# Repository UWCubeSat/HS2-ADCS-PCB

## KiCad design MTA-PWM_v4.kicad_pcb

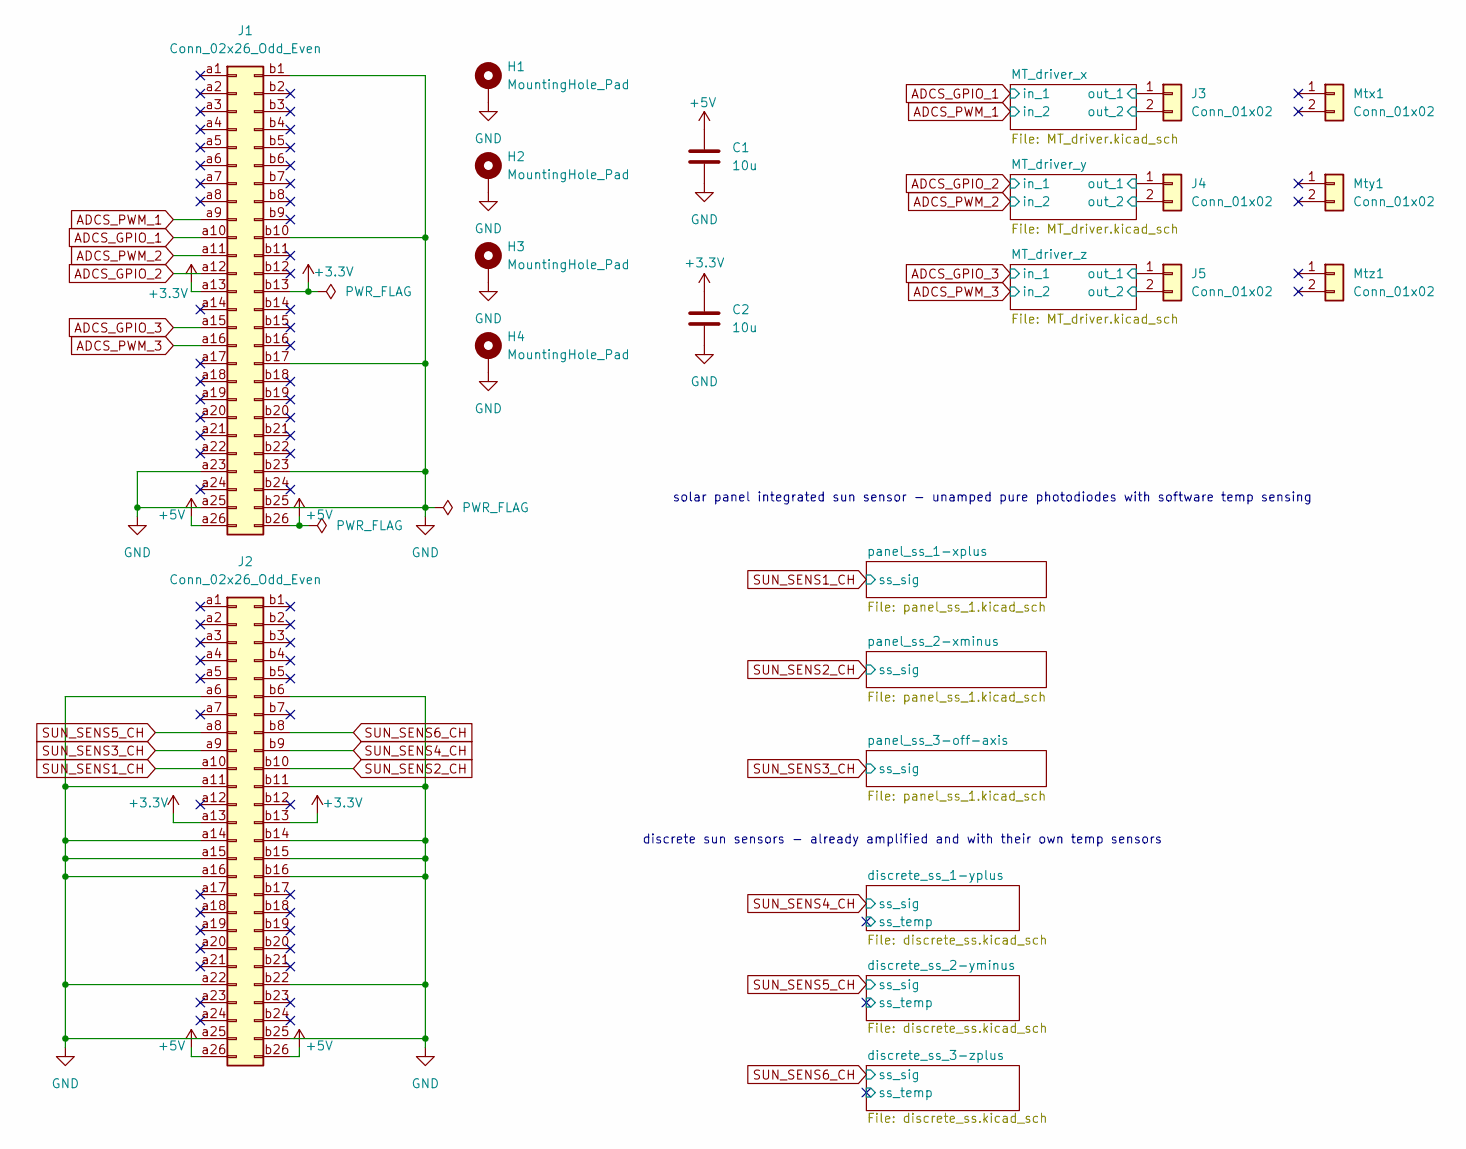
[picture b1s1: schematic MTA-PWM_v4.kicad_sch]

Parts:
C1, C2: 10u; C_Radial_D6.3mm_H11.0mm_P2.50mm
H1, H2, H3, H4: MountingHole_Pad; MountingHole_3.2mm_M3_Pad_TopBottom
J1, J2: Conn_02x26_Odd_Even; PC140Header_2x26_P2.54mm_Vertical
J3, J4: Conn_01x02; Molex_Pico-Lock_205338-0002_1x02-1MP_P2.00mm_Horizontal
J5: Conn_01x02; Molex_PicoBlade_53261-0271_1x02-1MP_P1.25mm_Horizontal
Mtx1: Conn_01x02; MT_CS0002-G2
Mty1: Conn_01x02; MT_CS0002-G2R
Mtz1: Conn_01x02; MTR_EXA

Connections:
+3.3V: C2.1, J1.a13, J1.b13, J2.a13, J2.b13; also elsewhere on the board
+5V: C1.1, J1.a26, J1.b26, J2.a26, J2.b26; also elsewhere on the board
/MT_driver_x/out_1: J3.1; also elsewhere on the board
/MT_driver_x/out_2: J3.2; also elsewhere on the board
/MT_driver_y/out_1: J4.1; also elsewhere on the board
/MT_driver_y/out_2: J4.2; also elsewhere on the board
/MT_driver_z/out_1: J5.1; also elsewhere on the board
/MT_driver_z/out_2: J5.2; also elsewhere on the board
ADCS_GPIO_1: J1.a10; also elsewhere on the board
ADCS_GPIO_2: J1.a12; also elsewhere on the board
ADCS_GPIO_3: J1.a15; also elsewhere on the board
ADCS_PWM_1: J1.a9; also elsewhere on the board
ADCS_PWM_2: J1.a11; also elsewhere on the board
ADCS_PWM_3: J1.a16; also elsewhere on the board
GND: C1.2, C2.2, H1.1 (1_1), H2.1 (1_1), H3.1 (1_1), H4.1 (1_1), J1.a23, J1.a25, J1.b1, J1.b10, J1.b17, J1.b23, J1.b25, J2.a6, J2.a11, J2.a14, J2.a15, J2.a16, J2.a22, J2.a25, J2.b6, J2.b11, J2.b14, J2.b15, J2.b16, J2.b22, J2.b25; also elsewhere on the board
SUN_SENS1_CH: J2.a10; also elsewhere on the board
SUN_SENS2_CH: J2.b10; also elsewhere on the board
SUN_SENS3_CH: J2.a9; also elsewhere on the board
SUN_SENS4_CH: J2.b9; also elsewhere on the board
SUN_SENS5_CH: J2.a8; also elsewhere on the board
SUN_SENS6_CH: J2.b8; also elsewhere on the board

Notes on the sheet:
solar panel integrated sun sensor - unamped pure photodiodes with software temp sensing
discrete sun sensors - already amplified and with their own temp sensors

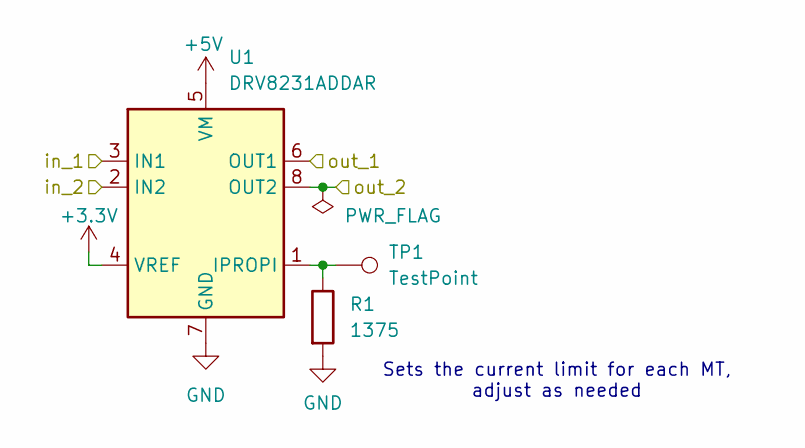
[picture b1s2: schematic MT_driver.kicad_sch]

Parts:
R1: 1375; R_Axial_DIN0207_L6.3mm_D2.5mm_P10.16mm_Horizontal
TP1: TestPoint; TestPoint_THTPad_1.5x1.5mm_Drill0.7mm
U1: DRV8231ADDAR; Texas_DSG0008A_WSON-8-1EP_2x2mm_P0.5mm_EP0.9x1.6mm

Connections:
+3.3V: U1.4 (VREF); also elsewhere on the board
+5V: U1.5 (VM); also elsewhere on the board
/MT_driver_x/out_1: U1.6 (OUT1); also elsewhere on the board
/MT_driver_x/out_2: U1.8 (OUT2); also elsewhere on the board
ADCS_GPIO_1: U1.3 (IN1); also elsewhere on the board
ADCS_PWM_1: U1.2 (IN2); also elsewhere on the board
GND: R1.2, U1.7 (GND), U1.9 (GND); also elsewhere on the board
unnamed: R1.1, TP1.1 (1_1), U1.1 (IPROPI)

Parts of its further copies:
R2, R3: 1375; R_Axial_DIN0207_L6.3mm_D2.5mm_P10.16mm_Horizontal
TP2, TP3: TestPoint; TestPoint_THTPad_1.5x1.5mm_Drill0.7mm
U2, U3: DRV8231ADDAR; Texas_DSG0008A_WSON-8-1EP_2x2mm_P0.5mm_EP0.9x1.6mm

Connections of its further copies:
+3.3V: U2.4 (VREF), U3.4 (VREF); also elsewhere on the board
+5V: U2.5 (VM), U3.5 (VM); also elsewhere on the board
/MT_driver_y/out_1: U2.6 (OUT1); also elsewhere on the board
/MT_driver_y/out_2: U2.8 (OUT2); also elsewhere on the board
/MT_driver_z/out_1: U3.6 (OUT1); also elsewhere on the board
/MT_driver_z/out_2: U3.8 (OUT2); also elsewhere on the board
ADCS_GPIO_2: U2.3 (IN1); also elsewhere on the board
ADCS_GPIO_3: U3.3 (IN1); also elsewhere on the board
ADCS_PWM_2: U2.2 (IN2); also elsewhere on the board
ADCS_PWM_3: U3.2 (IN2); also elsewhere on the board
GND: R2.2, R3.2, U2.7 (GND), U2.9 (GND), U3.7 (GND), U3.9 (GND); also elsewhere on the board
unnamed: R2.1, TP2.1 (1_1), U2.1 (IPROPI)
unnamed: R3.1, TP3.1 (1_1), U3.1 (IPROPI)

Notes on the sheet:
Sets the current limit for each MT, adjust as needed

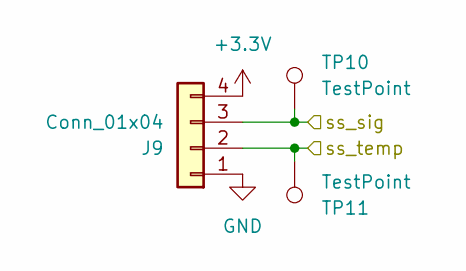
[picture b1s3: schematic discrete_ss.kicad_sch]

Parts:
J9: Conn_01x04; Molex_Pico-Lock_205338-0004_1x04-1MP_P2.00mm_Horizontal
TP10, TP11: TestPoint; TestPoint_THTPad_1.5x1.5mm_Drill0.7mm

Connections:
+3.3V: J9.4; also elsewhere on the board
/discrete_ss_1-yplus/ss_temp: J9.2, TP11.1 (1_1)
GND: J9.1; also elsewhere on the board
SUN_SENS4_CH: J9.3, TP10.1 (1_1); also elsewhere on the board

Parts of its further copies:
J10, J11: Conn_01x04; Molex_Pico-Lock_205338-0004_1x04-1MP_P2.00mm_Horizontal
TP12, TP13, TP14, TP15: TestPoint; TestPoint_THTPad_1.5x1.5mm_Drill0.7mm

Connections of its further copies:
+3.3V: J10.4, J11.4; also elsewhere on the board
/discrete_ss_2-yminus/ss_temp: J10.2, TP13.1 (1_1)
/discrete_ss_3-zplus/ss_temp: J11.2, TP15.1 (1_1)
GND: J10.1, J11.1; also elsewhere on the board
SUN_SENS5_CH: J10.3, TP12.1 (1_1); also elsewhere on the board
SUN_SENS6_CH: J11.3, TP14.1 (1_1); also elsewhere on the board

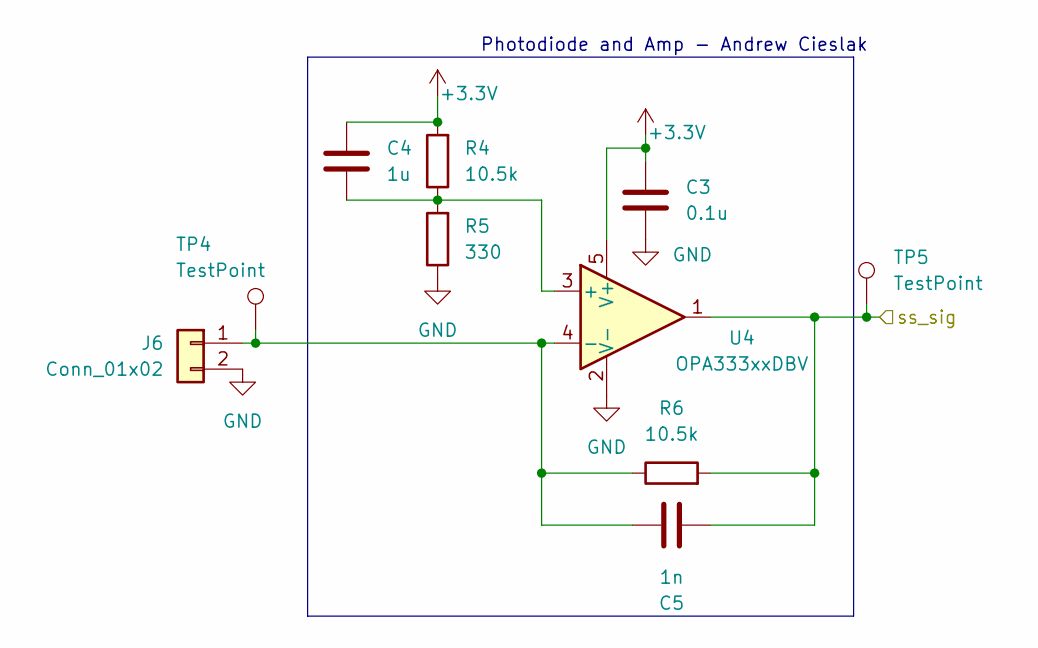
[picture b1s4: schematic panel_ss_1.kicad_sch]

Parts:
C3: 0.1u; C_0603_1608Metric
C4: 1u; C_0603_1608Metric
C5: 1n; C_0402_1005Metric
J6: Conn_01x02; Molex_Pico-Lock_205338-0002_1x02-1MP_P2.00mm_Horizontal
R4, R6: 10.5k; R_0402_1005Metric
R5: 330; R_0402_1005Metric
TP4, TP5: TestPoint; TestPoint_THTPad_1.5x1.5mm_Drill0.7mm
U4: OPA333xxDBV; SOT-23-5

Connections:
+3.3V: C3.1, C4.1, R4.2, U4.5 (V+); also elsewhere on the board
GND: C3.2, J6.2, R5.1, U4.2 (V-); also elsewhere on the board
unnamed: C5.2, J6.1, R6.1, TP4.1 (1_1), U4.4 (-)
unnamed: C4.2, R4.1, R5.2, U4.3 (+)
SUN_SENS1_CH: C5.1, R6.2, TP5.1 (1_1), U4.1; also elsewhere on the board

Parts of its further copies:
C6, C9: 0.1u; C_0603_1608Metric
C7, C10: 1u; C_0603_1608Metric
C8, C11: 1n; C_0402_1005Metric
J7, J8: Conn_01x02; Molex_Pico-Lock_205338-0002_1x02-1MP_P2.00mm_Horizontal
R7, R9, R10, R12: 10.5k; R_0402_1005Metric
R8, R11: 330; R_0402_1005Metric
TP6, TP7, TP8, TP9: TestPoint; TestPoint_THTPad_1.5x1.5mm_Drill0.7mm
U5, U6: OPA333xxDBV; SOT-23-5

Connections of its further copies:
+3.3V: C6.1, C7.1, C9.1, C10.1, R7.2, R10.2, U5.5 (V+), U6.5 (V+); also elsewhere on the board
GND: C6.2, C9.2, J7.2, J8.2, R8.1, R11.1, U5.2 (V-), U6.2 (V-); also elsewhere on the board
unnamed: C8.2, J7.1, R9.1, TP6.1 (1_1), U5.4 (-)
unnamed: C11.2, J8.1, R12.1, TP8.1 (1_1), U6.4 (-)
unnamed: C7.2, R7.1, R8.2, U5.3 (+)
unnamed: C10.2, R10.1, R11.2, U6.3 (+)
SUN_SENS2_CH: C8.1, R9.2, TP7.1 (1_1), U5.1; also elsewhere on the board
SUN_SENS3_CH: C11.1, R12.2, TP9.1 (1_1), U6.1; also elsewhere on the board

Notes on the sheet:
Photodiode and Amp - Andrew Cieslak

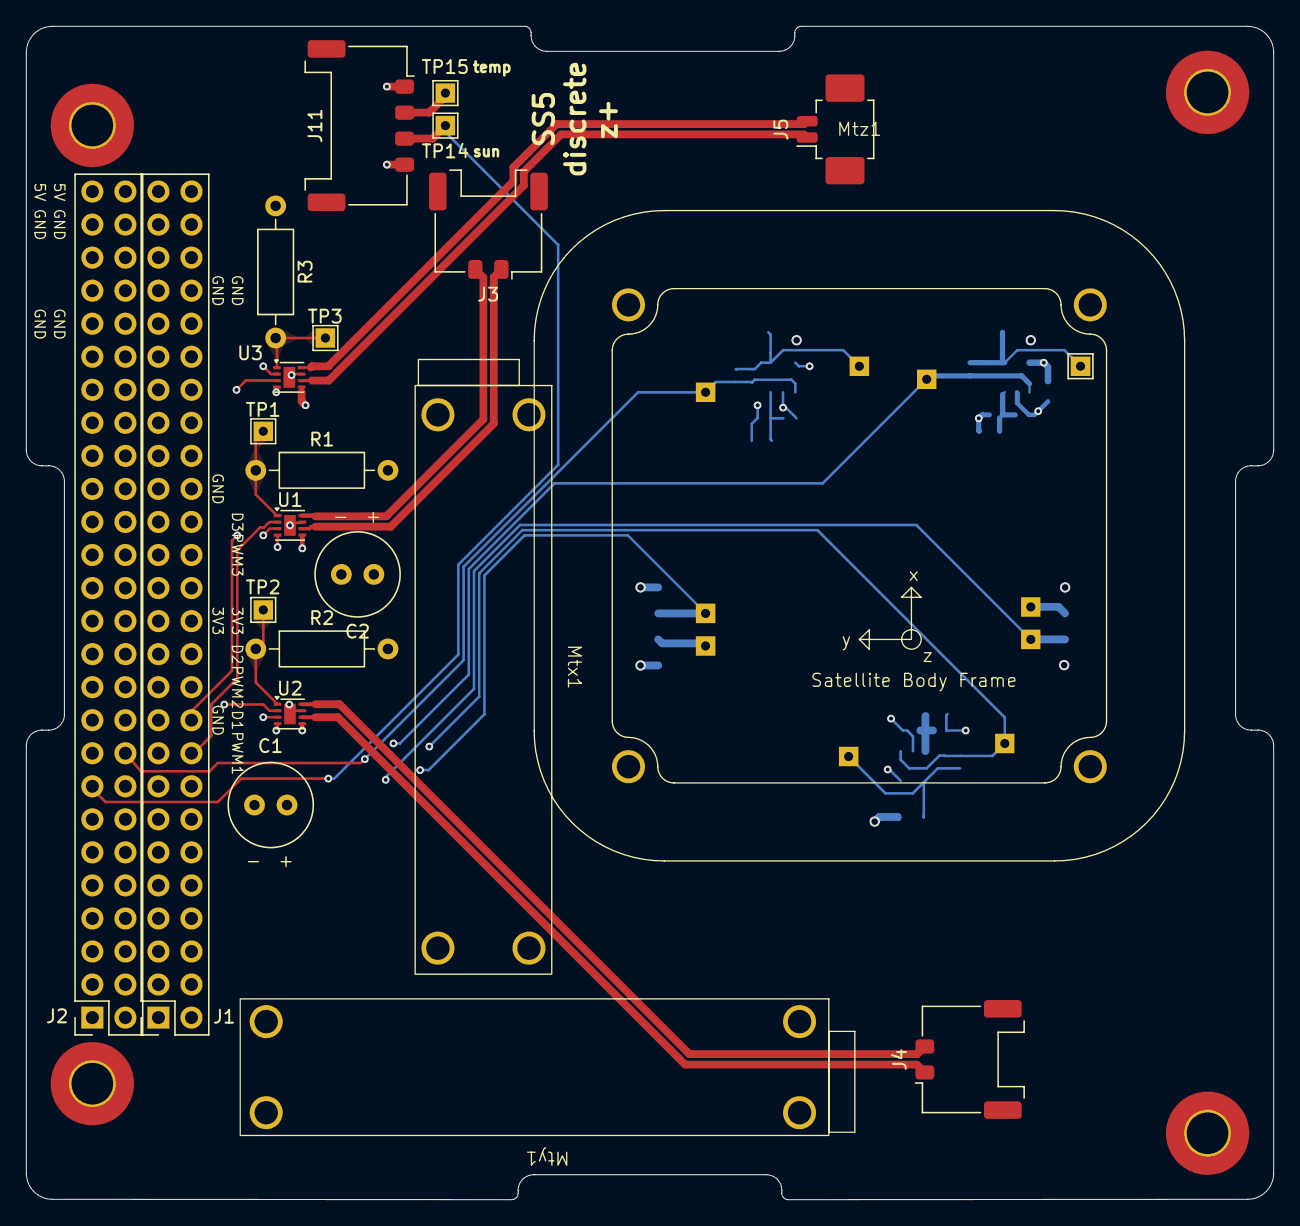
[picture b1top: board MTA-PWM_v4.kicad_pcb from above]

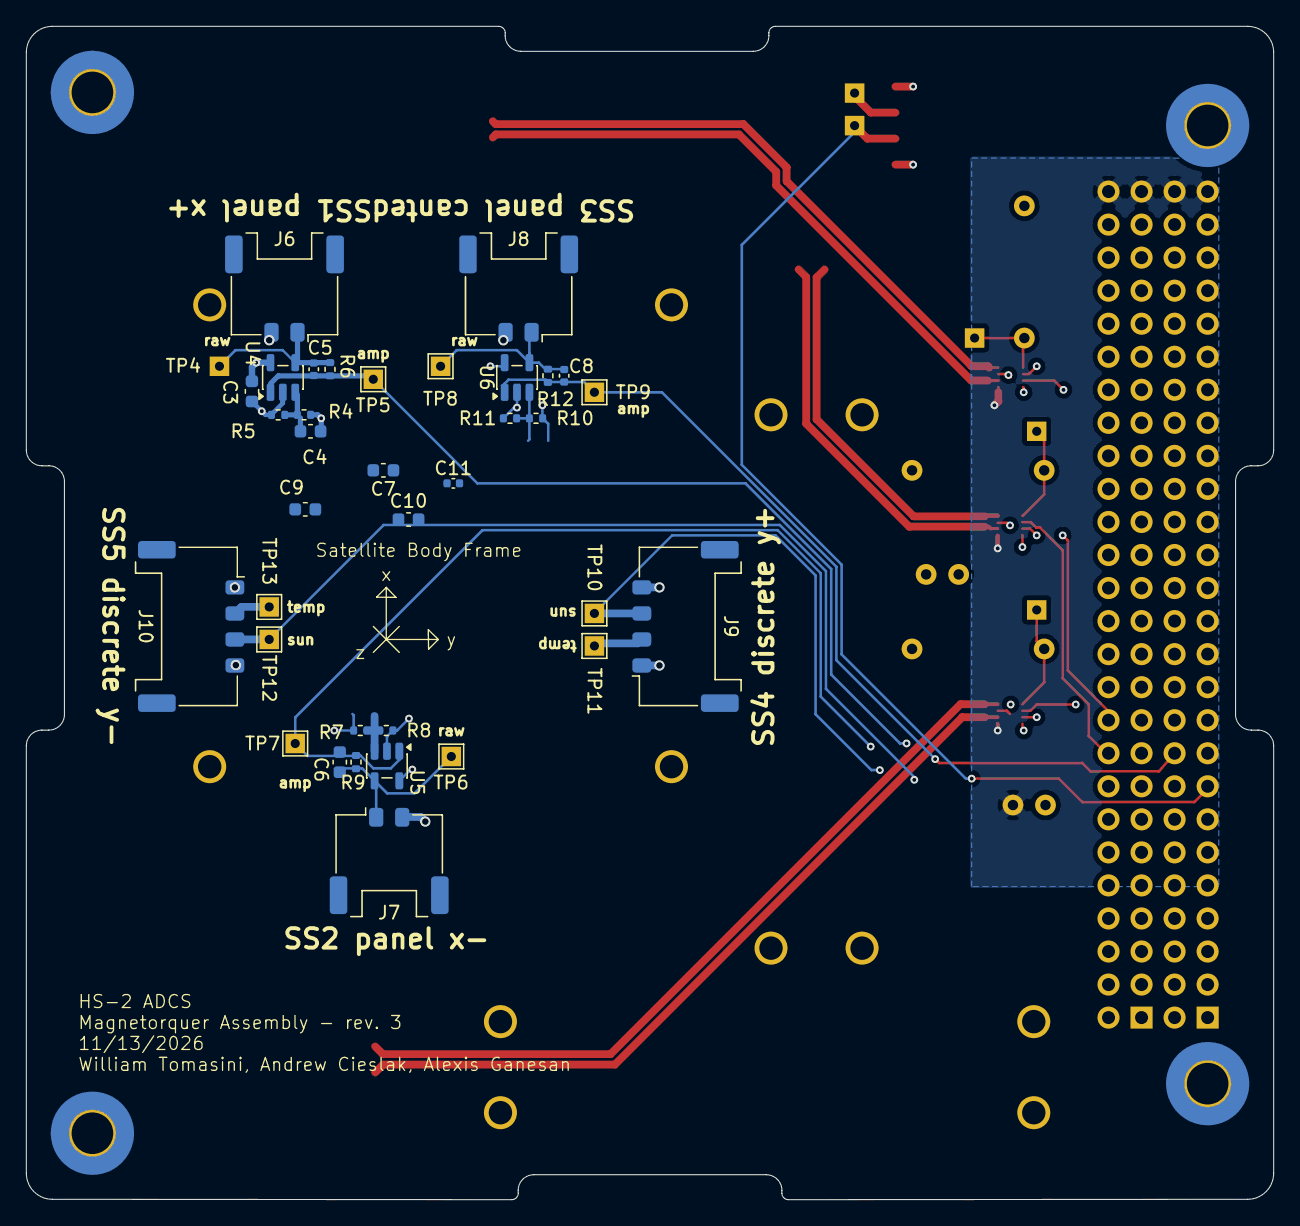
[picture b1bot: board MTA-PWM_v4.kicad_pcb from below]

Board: 4 copper layers, 95.9 x 90.2 mm, 62 parts (35 on the bottom side), 33 nets.

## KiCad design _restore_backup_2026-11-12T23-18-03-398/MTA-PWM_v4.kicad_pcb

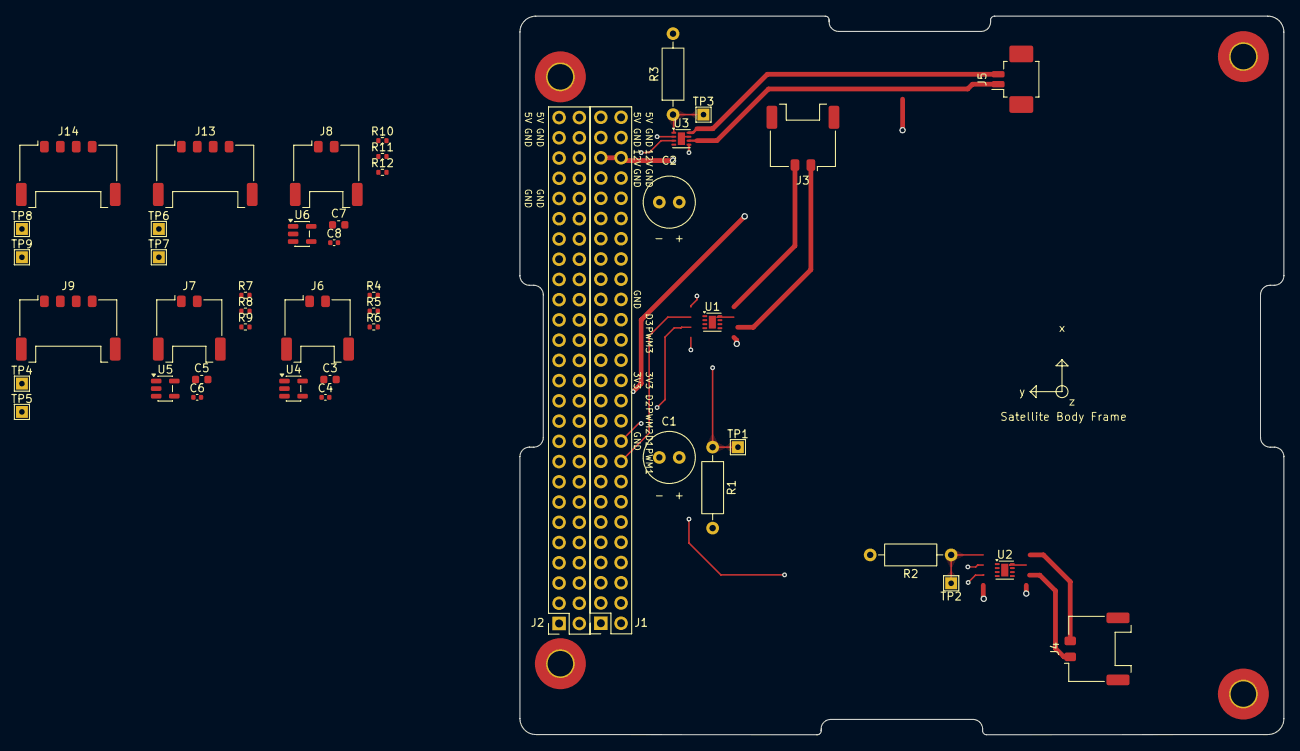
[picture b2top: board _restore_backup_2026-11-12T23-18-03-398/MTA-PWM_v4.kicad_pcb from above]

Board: 4 copper layers, 95.9 x 90.2 mm, 50 parts (0 on the bottom side), 34 nets.

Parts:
C1, C2: 10u; C_Radial_D6.3mm_H11.0mm_P2.50mm
C3, C5, C7: 1u; C_0603_1608Metric
C4, C6, C8: 1n; C_0402_1005Metric
H1, H2, H3, H4: MountingHole_Pad; MountingHole_3.2mm_M3_Pad_TopBottom
J1, J2: Conn_02x26_Odd_Even; PC140Header_2x26_P2.54mm_Vertical
J3, J4, J6, J7, J8: Conn_01x02; Molex_Pico-Lock_205338-0002_1x02-1MP_P2.00mm_Horizontal
J5: Conn_01x02; Molex_PicoBlade_53261-0271_1x02-1MP_P1.25mm_Horizontal
J9, J13, J14: Conn_01x04; Molex_Pico-Lock_205338-0004_1x04-1MP_P2.00mm_Horizontal
R1, R2, R3: 1375; R_Axial_DIN0207_L6.3mm_D2.5mm_P10.16mm_Horizontal
R4, R6, R7, R9, R10, R12: 10.5k; R_0402_1005Metric
R5, R8, R11: 330; R_0402_1005Metric
TP1, TP2, TP3, TP4, TP5, TP6, TP7, TP8, TP9: TestPoint; TestPoint_THTPad_1.5x1.5mm_Drill0.7mm
U1, U2, U3: DRV8231ADDAR; Texas_DSG0008A_WSON-8-1EP_2x2mm_P0.5mm_EP0.9x1.6mm
U4, U5, U6: OPA333xxDBV; SOT-23-5

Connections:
+3.3V: C3.1, C5.1, C7.1, J1.a13, J1.b13, J2.a13, J2.b13, J9.4, J13.4, J14.4, R4.2, R7.2, R10.2, U1.4 (VREF), U2.4 (VREF), U3.4 (VREF), U4.5 (V+), U5.5 (V+), U6.5 (V+)
+5V: C1.1, J1.a26, J1.b26, J2.a26, J2.b26, U1.5 (VM), U2.5 (VM)
+12V: C2.1, J1.a24, J1.b24, J2.a12, J2.b12, U3.5 (VM)
/discrete_ss_1-yplus/ss_temp: J9.2, TP5.1 (1_1)
/discrete_ss_2-yminus/ss_temp: J13.2, TP7.1 (1_1)
/discrete_ss_3-zplus/ss_temp: J14.2, TP9.1 (1_1)
ADCS_GPIO_1: J1.a10, U1.3 (IN1)
ADCS_GPIO_2: J1.a12, U2.3 (IN1)
ADCS_GPIO_3: J1.a16, U3.3 (IN1)
ADCS_PWM_1: J1.a9, U1.2 (IN2)
ADCS_PWM_2: J1.a11, U2.2 (IN2)
ADCS_PWM_3: J1.a15, U3.2 (IN2)
GND: C1.2, C2.2, H1.1 (1_1), H2.1 (1_1), H3.1 (1_1), H4.1 (1_1), J1.a23, J1.a25, J1.b1, J1.b10, J1.b17, J1.b23, J1.b25, J2.a6, J2.a11, J2.a14, J2.a15, J2.a16, J2.a22, J2.a25, J2.b6, J2.b11, J2.b14, J2.b15, J2.b16, J2.b22, J2.b25, J6.2, J7.2, J8.2, J9.1, J13.1, J14.1, R1.2, R2.2, R3.2, R5.1, R8.1, R11.1, U1.7 (GND), U1.9 (GND), U2.7 (GND), U2.9 (GND), U3.7 (GND), U3.9 (GND), U4.2 (V-), U5.2 (V-), U6.2 (V-)
unnamed: J3.1, U1.6 (OUT1)
unnamed: J3.2, U1.8 (OUT2)
unnamed: J4.1, U2.6 (OUT1)
unnamed: J4.2, U2.8 (OUT2)
unnamed: J5.1, U3.6 (OUT1)
unnamed: J5.2, U3.8 (OUT2)
unnamed: C4.1, J6.1, R6.1, U4.3 (+)
unnamed: C6.1, J7.1, R9.1, U5.3 (+)
unnamed: C8.1, J8.1, R12.1, U6.3 (+)
unnamed: R1.1, TP1.1 (1_1), U1.1 (IPROPI)
unnamed: R2.1, TP2.1 (1_1), U2.1 (IPROPI)
unnamed: R3.1, TP3.1 (1_1), U3.1 (IPROPI)
unnamed: C3.2, R4.1, R5.2, U4.4 (-)
unnamed: C5.2, R7.1, R8.2, U5.4 (-)
unnamed: C7.2, R10.1, R11.2, U6.4 (-)
SUN_SENS1_CH: C4.2, J2.a10, R6.2, U4.1
SUN_SENS2_CH: C6.2, J2.b10, R9.2, U5.1
SUN_SENS3_CH: C8.2, J2.a9, R12.2, U6.1
SUN_SENS4_CH: J2.b9, J9.3, TP4.1 (1_1)
SUN_SENS5_CH: J2.a8, J13.3, TP6.1 (1_1)
SUN_SENS6_CH: J2.b8, J14.3, TP8.1 (1_1)

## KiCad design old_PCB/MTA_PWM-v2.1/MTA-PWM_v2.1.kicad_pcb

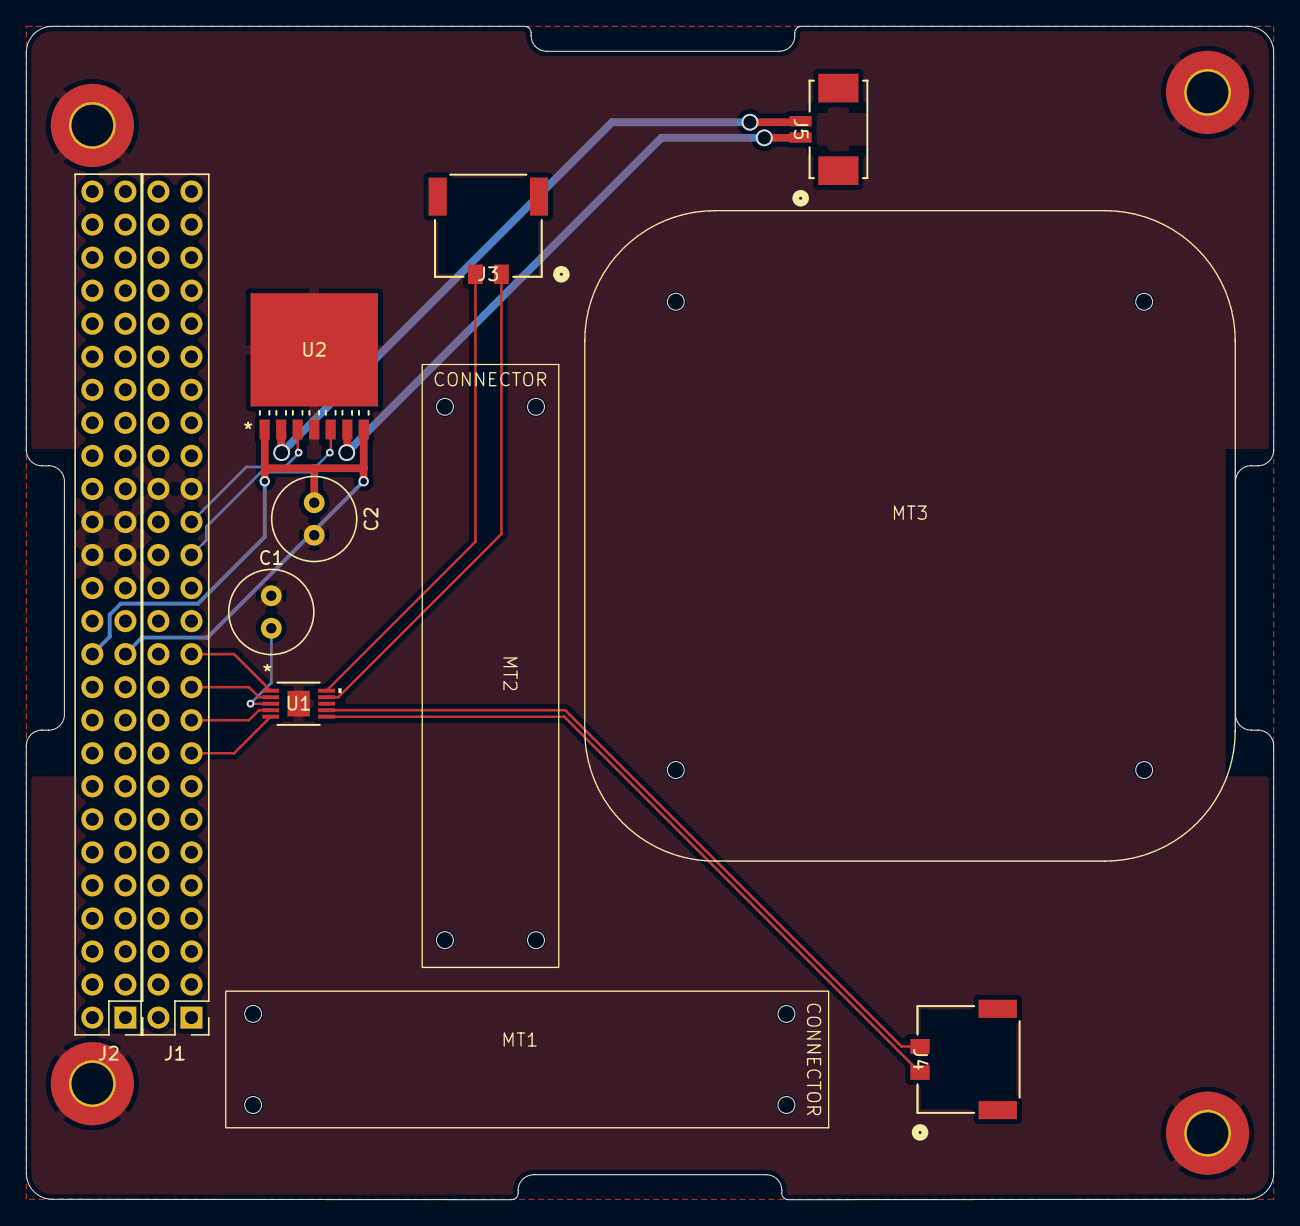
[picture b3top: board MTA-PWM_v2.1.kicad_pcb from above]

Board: 2 copper layers, 95.9 x 90.2 mm, 16 parts (0 on the bottom side), 20 nets.

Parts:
C1, C2: 10u; C_Radial_D6.3mm_H11.0mm_P2.50mm
H1, H2, H3, H4: MountingHole_Pad; MountingHole_3.2mm_M3_Pad_TopBottom
J1, J2: Conn_02x26_Odd_Even; pc104-PinSocket_2x26_P2.54mm_Vertical
J3, J4: 2053380002; CONN_2053380000-SD_02_MOL
J5: 532610271; CONN_532610001-SD_02_MOL
MT1, MT2: CS-cubetorquer
MT3: MTR-satsearch
U1: A3909GLYTR-T; A3909GLYTR-T_ALM
U2: BD6222HFP-TR; HRP7_ROM

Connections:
3.3V: J2.27, J2.28
5V_PERM: C1.1, J1.25, J1.26, J2.25, J2.26, U1.3 (VBB)
12V: C2.1, J2.23, J2.24, U2.1 (VREF), U2.7 (VCC)
ACDS_PWM_1: J1.17, U1.5 (IN4)
ACDS_PWM_2: J1.19, U1.4 (IN3)
ACDS_PWM_3: J1.21, U1.2 (IN2)
ACDS_PWM_4: J1.23, U1.1 (IN1)
ACDS_PWM_5: J1.29, U2.5 (RIN)
ACDS_PWM_6: J1.31, U2.3 (FIN)
BATT_PIN: J2.45, J2.47
GND: C1.2, C2.2, H1.1, H2.1, H3.1, H4.1, J1.33, J1.34, J2.29, J2.30, J2.31, J2.32, U1.8 (GND), U1.EPAD, U2.4 (GND), U2.8 (EPAD)
unnamed: J3.2, U1.10 (OUT1)
unnamed: J3.1, U1.9 (OUT2)
unnamed: J4.2, U1.7 (OUT3)
unnamed: J4.1, U1.6 (OUT4)
unnamed: J5.2, U2.2 (OUT1)
unnamed: J5.1, U2.6 (OUT2)
RS-485 SYS1 B: J1.22, J1.24
SOL_PIN: J2.43, J2.44
SYS_PIN: J2.46, J2.48

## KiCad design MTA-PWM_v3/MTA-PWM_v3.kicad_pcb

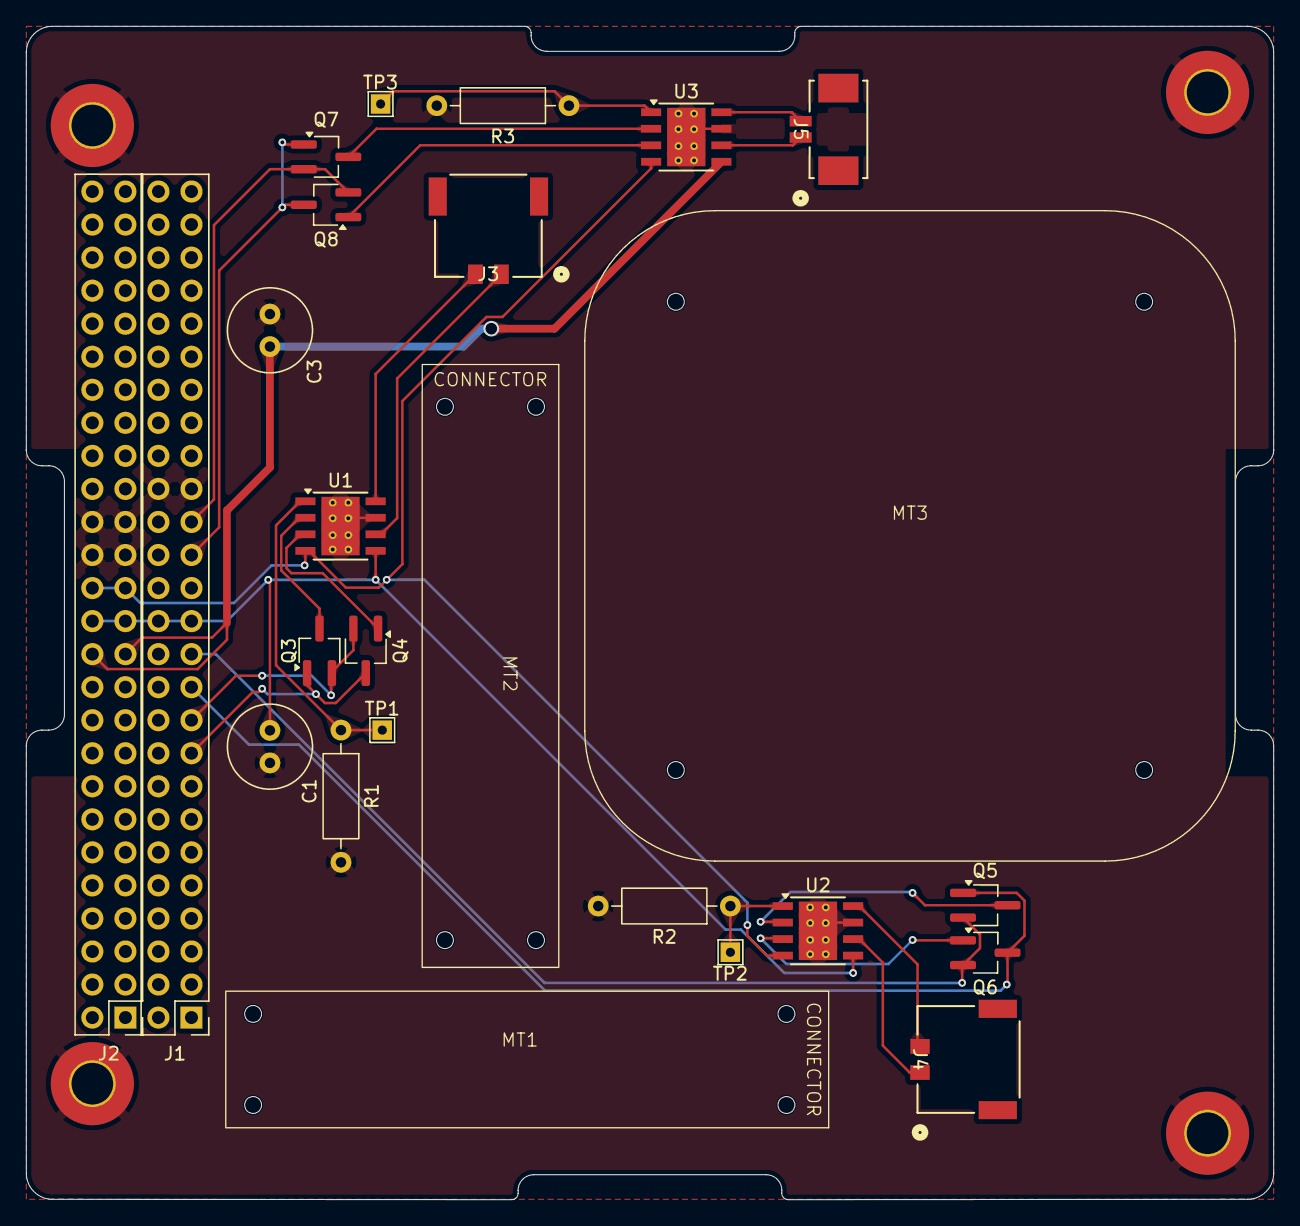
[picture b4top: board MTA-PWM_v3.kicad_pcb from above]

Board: 2 copper layers, 95.9 x 90.2 mm, 29 parts (0 on the bottom side), 29 nets.

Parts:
C1, C3: 10u; C_Radial_D6.3mm_H11.0mm_P2.50mm
H1, H2, H3, H4: MountingHole_Pad; MountingHole_3.2mm_M3_Pad_TopBottom
J1, J2: Conn_02x26_Odd_Even; pc104-PinSocket_2x26_P2.54mm_Vertical
J3, J4: 2053380002; CONN_2053380000-SD_02_MOL
J5: 532610271; CONN_532610001-SD_02_MOL
MT1, MT2: CS-cubetorquer
MT3: MTR-satsearch
Q3, Q5, Q7: NMOS; TSOT-23_HandSoldering
Q4, Q6, Q8: PMOS; TSOT-23_HandSoldering
R1, R2, R3: 1375; R_Axial_DIN0207_L6.3mm_D2.5mm_P10.16mm_Horizontal
TP1, TP2, TP3: TestPoint; TestPoint_THTPad_1.5x1.5mm_Drill0.7mm
U1, U2, U3: DRV8231ADDAR; TI_SO-PowerPAD-8_ThermalVias

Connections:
3.3V: J2.27, J2.28, U1.4 (VREF), U2.4 (VREF), U3.4 (VREF)
5V_PERM: C1.1, J1.25, J1.26, J2.25, J2.26, U1.5 (VM), U2.5 (VM)
12V: C3.1, J2.23, J2.24, U3.5 (VM)
ACDS_GPIO_1: J1.19, Q3.2 (G), Q4.2 (G)
ACDS_GPIO_2: J1.23, Q5.2 (G), Q6.2 (G)
ACDS_GPIO_3: J1.31, Q7.2 (G), Q8.2 (G)
ACDS_PWM_1: J1.17, Q3.1 (D), Q4.3 (S)
ACDS_PWM_2: J1.21, Q5.1 (D), Q6.3 (S)
ACDS_PWM_3: J1.29, Q7.1 (D), Q8.3 (S)
BATT_PIN: J2.45, J2.47
GND: C1.2, C3.2, H1.1, H2.1, H3.1, H4.1, J1.33, J1.34, J2.29, J2.30, J2.31, J2.32, R1.2, R2.2, R3.2, U1.7 (GND), U1.9 (GND), U2.7 (GND), U2.9 (GND), U3.7 (GND), U3.9 (GND)
unnamed: Q3.3 (S), U1.2 (IN2)
unnamed: Q4.1 (D), U1.3 (IN1)
unnamed: Q5.3 (S), U2.2 (IN2)
unnamed: Q6.1 (D), U2.3 (IN1)
unnamed: Q7.3 (S), U3.2 (IN2)
unnamed: Q8.1 (D), U3.3 (IN1)
unnamed: R1.1, TP1.1 (1_1), U1.1 (IPROPI)
unnamed: J3.1, U1.6 (OUT1)
unnamed: J3.2, U1.8 (OUT2)
unnamed: R2.1, TP2.1 (1_1), U2.1 (IPROPI)
unnamed: J4.1, U2.6 (OUT1)
unnamed: J4.2, U2.8 (OUT2)
unnamed: R3.1, TP3.1 (1_1), U3.1 (IPROPI)
unnamed: J5.1, U3.6 (OUT1)
unnamed: J5.2, U3.8 (OUT2)
RS-485 SYS1 B: J1.22, J1.24
SOL_PIN: J2.43, J2.44
SYS_PIN: J2.46, J2.48
